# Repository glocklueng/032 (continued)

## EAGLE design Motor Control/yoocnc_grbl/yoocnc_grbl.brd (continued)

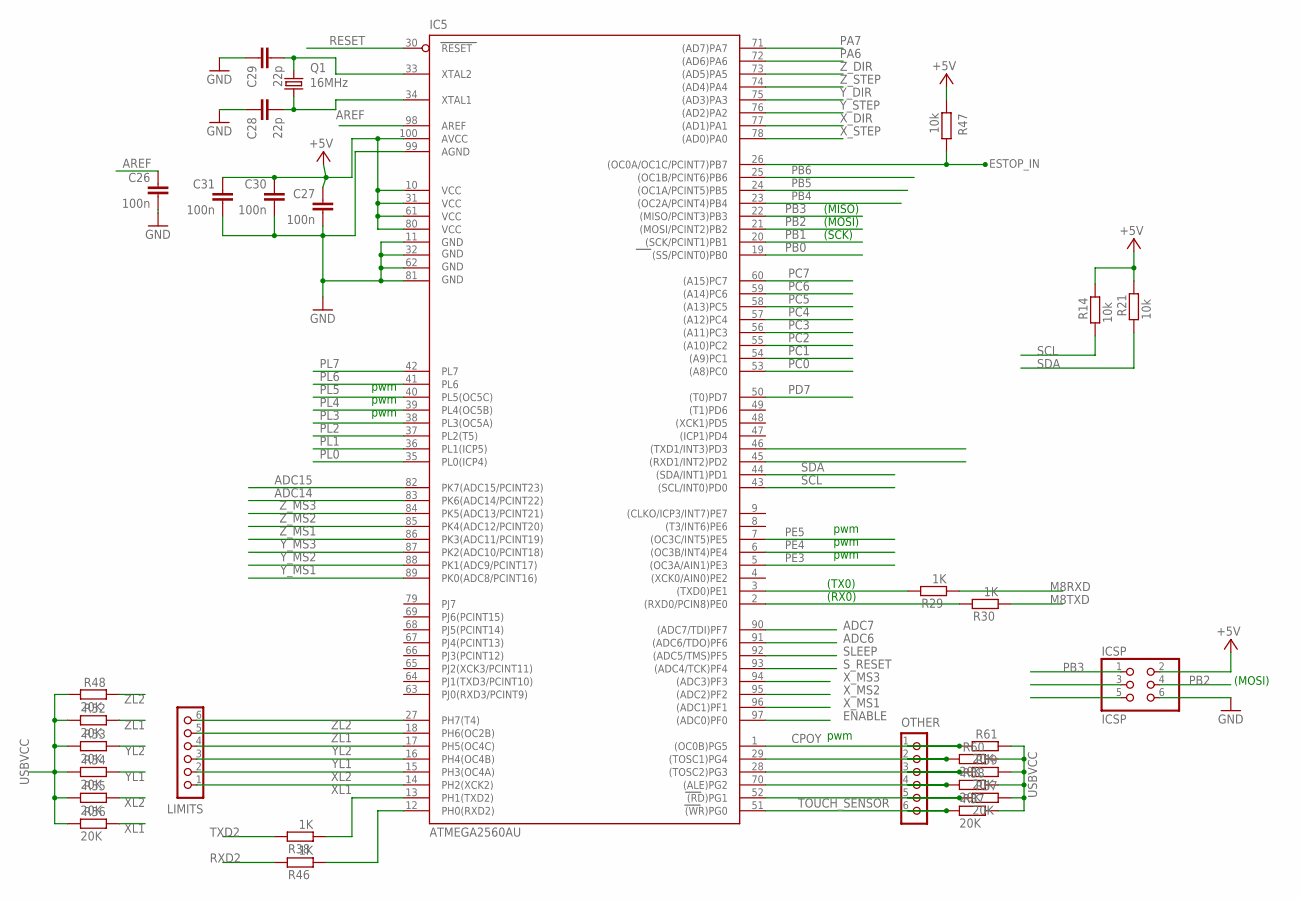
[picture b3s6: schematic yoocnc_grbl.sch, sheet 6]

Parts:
C26, C27, C30, C31: 100n; C0805K; PARTNO CC0805ZRY5V9BB104
C28, C29: 22p; C0805K; PARTNO C0805C220J5GACTU
IC5: ATMEGA2560AU; TQFP100; PARTNO ATMEGA256RZBV-8AU
ICSP: ICSP; 2X03; PARTNO *
LIMITS: CON_HEADER_1X06-PTH; M1X6; PARTNO *
OTHER: CON_HEADER_1X06-PTH; M1X6; PARTNO *
Q1: 16MHz; SM49; PARTNO ABLS-16.000MHZ-B4-T
R14, R21, R47: 10k; R0805W; PARTNO RC0805JR-0710KL
R29, R30, R38, R46: 1K; R0805W; PARTNO RC0805JR-0710KL
R37, R48, R52, R53, R54, R55, R56, R57, R58, R59, R60, R61: 20K; R0603; PARTNO RC0805JR-0710KL

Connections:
ADC6: IC5.91 ((ADC6/TDO)PF6)
ADC7: IC5.90 ((ADC7/TDI)PF7)
ADC14: IC5.83 (PK6(ADC14/PCINT22))
ADC15: IC5.82 (PK7(ADC15/PCINT23))
AREF: C26.1, IC5.98 (AREF)
CPOY: IC5.1 ((OC0B)PG5), OTHER.1, R61.2
ENABLE: IC5.97 ((ADC0)PF0); also elsewhere on the board
ESTOP_IN: IC5.26 ((OC0A/OC1C/PCINT7)PB7), R47.1; also elsewhere on the board
GND: C26.2, C27.2, C28.1, C29.1, C30.2, C31.2, IC5.11 (GND), IC5.32 (GND1), IC5.62 (GND2), IC5.81 (GND3), IC5.99 (AGND), ICSP.6; also elsewhere on the board
M8RXD: R29.2; also elsewhere on the board
M8TXD: R30.2; also elsewhere on the board
unnamed: IC5.29 ((TOSC1)PG4), OTHER.2, R60.2
unnamed: IC5.28 ((TOSC2)PG3), OTHER.3, R59.2
unnamed: IC5.3 ((TXD0)PE1), R29.1
unnamed: IC5.2 ((RXD0/PCIN8)PE0), R30.1
unnamed: IC5.70 ((ALE)PG2), OTHER.4, R58.2
unnamed: IC5.52 ((RD)PG1), OTHER.5, R57.2
unnamed: IC5.13 (PH1(TXD2)), R38.2
unnamed: IC5.12 (PH0(RXD2)), R46.2
unnamed: C28.2, IC5.34 (XTAL1)
unnamed: C29.2, IC5.33 (XTAL2)
PA6: IC5.72 ((AD6)PA6)
PA7: IC5.71 ((AD7)PA7)
PB0: IC5.19 ((SS/PCINT0)PB0)
PB1: IC5.20 ((SCK/PCINT1)PB1), ICSP.3
PB2: IC5.21 ((MOSI/PCINT2)PB2), ICSP.4
PB3: IC5.22 ((MISO/PCINT3)PB3), ICSP.1
PB4: IC5.23 ((OC2A/PCINT4)PB4)
PB5: IC5.24 ((OC1A/PCINT5)PB5)
PB6: IC5.25 ((OC1B/PCINT6)PB6)
PC0: IC5.53 ((A8)PC0)
PC1: IC5.54 ((A9)PC1)
PC2: IC5.55 ((A10)PC2)
PC3: IC5.56 ((A11)PC3)
PC4: IC5.57 ((A12)PC4)
PC5: IC5.58 ((A13)PC5)
PC6: IC5.59 ((A14)PC6)
PC7: IC5.60 ((A15)PC7)
PD7: IC5.50 ((T0)PD7)
PE3: IC5.5 ((OC3A/AIN1)PE3)
PE4: IC5.6 ((OC3B/INT4)PE4)
PE5: IC5.7 ((OC3C/INT5)PE5)
PL0: IC5.35 (PL0(ICP4))
PL1: IC5.36 (PL1(ICP5))
PL2: IC5.37 (PL2(T5))
PL3: IC5.38 (PL3(OC5A))
PL4: IC5.39 (PL4(OC5B))
PL5: IC5.40 (PL5(OC5C))
PL6: IC5.41 (PL6)
PL7: IC5.42 (PL7)
RESET: IC5.30 (RESET), ICSP.5; also elsewhere on the board
RXD1: IC5.45 ((RXD1/INT2)PD2)
RXD2: R46.1; also elsewhere on the board
SCL: IC5.43 ((SCL/INT0)PD0), R14.2
SDA: IC5.44 ((SDA/INT1)PD1), R21.2
SLEEP: IC5.92 ((ADC5/TMS)PF5); also elsewhere on the board
S_RESET: IC5.93 ((ADC4/TCK)PF4); also elsewhere on the board
TOUCH_SENSOR: IC5.51 ((WR)PG0), OTHER.6, R37.2
TXD1: IC5.46 ((TXD1/INT3)PD3)
TXD2: R38.1; also elsewhere on the board
USBVCC: C27.1, C30.1, C31.1, IC5.10 (VCC), IC5.31 (VCC1), IC5.61 (VCC2), IC5.80 (VCC3), IC5.100 (AVCC), ICSP.2, R14.1, R21.1, R37.1, R47.2, R48.2, R52.2, R53.2, R54.2, R55.2, R56.2, R57.1, R58.1, R59.1, R60.1, R61.1; also elsewhere on the board
XL1: IC5.14 (PH2(XCK2)), LIMITS.1, R56.1
XL2: IC5.15 (PH3(OC4A)), LIMITS.2, R55.1
X_DIR: IC5.77 ((AD1)PA1); also elsewhere on the board
X_MS1: IC5.96 ((ADC1)PF1); also elsewhere on the board
X_MS2: IC5.95 ((ADC2)PF2); also elsewhere on the board
X_MS3: IC5.94 ((ADC3)PF3); also elsewhere on the board
X_STEP: IC5.78 ((AD0)PA0); also elsewhere on the board
YL1: IC5.16 (PH4(OC4B)), LIMITS.3, R54.1
YL2: IC5.17 (PH5(OC4C)), LIMITS.4, R53.1
Y_DIR: IC5.75 ((AD3)PA3); also elsewhere on the board
Y_MS1: IC5.89 (PK0(ADC8/PCINT16)); also elsewhere on the board
Y_MS2: IC5.88 (PK1(ADC9/PCINT17)); also elsewhere on the board
Y_MS3: IC5.87 (PK2(ADC10/PCINT18)); also elsewhere on the board
Y_STEP: IC5.76 ((AD2)PA2); also elsewhere on the board
ZL1: IC5.18 (PH6(OC2B)), LIMITS.5, R52.1
ZL2: IC5.27 (PH7(T4)), LIMITS.6, R48.1
Z_DIR: IC5.73 ((AD5)PA5); also elsewhere on the board
Z_MS1: IC5.86 (PK3(ADC11/PCINT19)); also elsewhere on the board
Z_MS2: IC5.85 (PK4(ADC12/PCINT20)); also elsewhere on the board
Z_MS3: IC5.84 (PK5(ADC13/PCINT21)); also elsewhere on the board
Z_STEP: IC5.74 ((AD4)PA4); also elsewhere on the board

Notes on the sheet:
pwm
(TX0)
(RX0)
(MISO)
(SCK)
(MOSI)

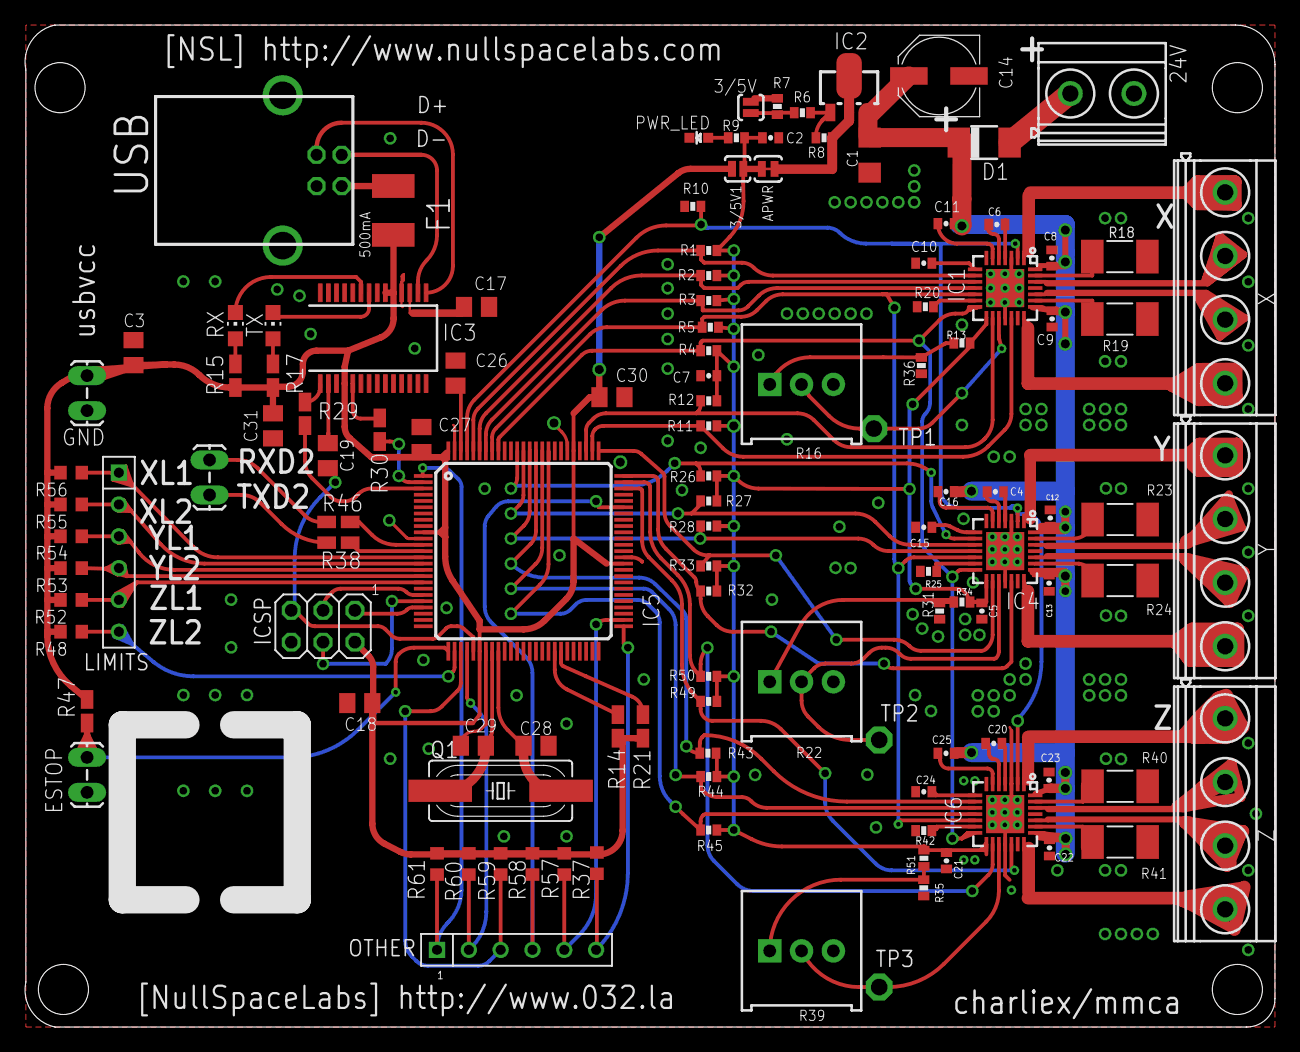
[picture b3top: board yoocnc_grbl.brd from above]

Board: 2 copper layers, 99.8 x 80.0 mm, 121 parts (0 on the bottom side), 105 nets.

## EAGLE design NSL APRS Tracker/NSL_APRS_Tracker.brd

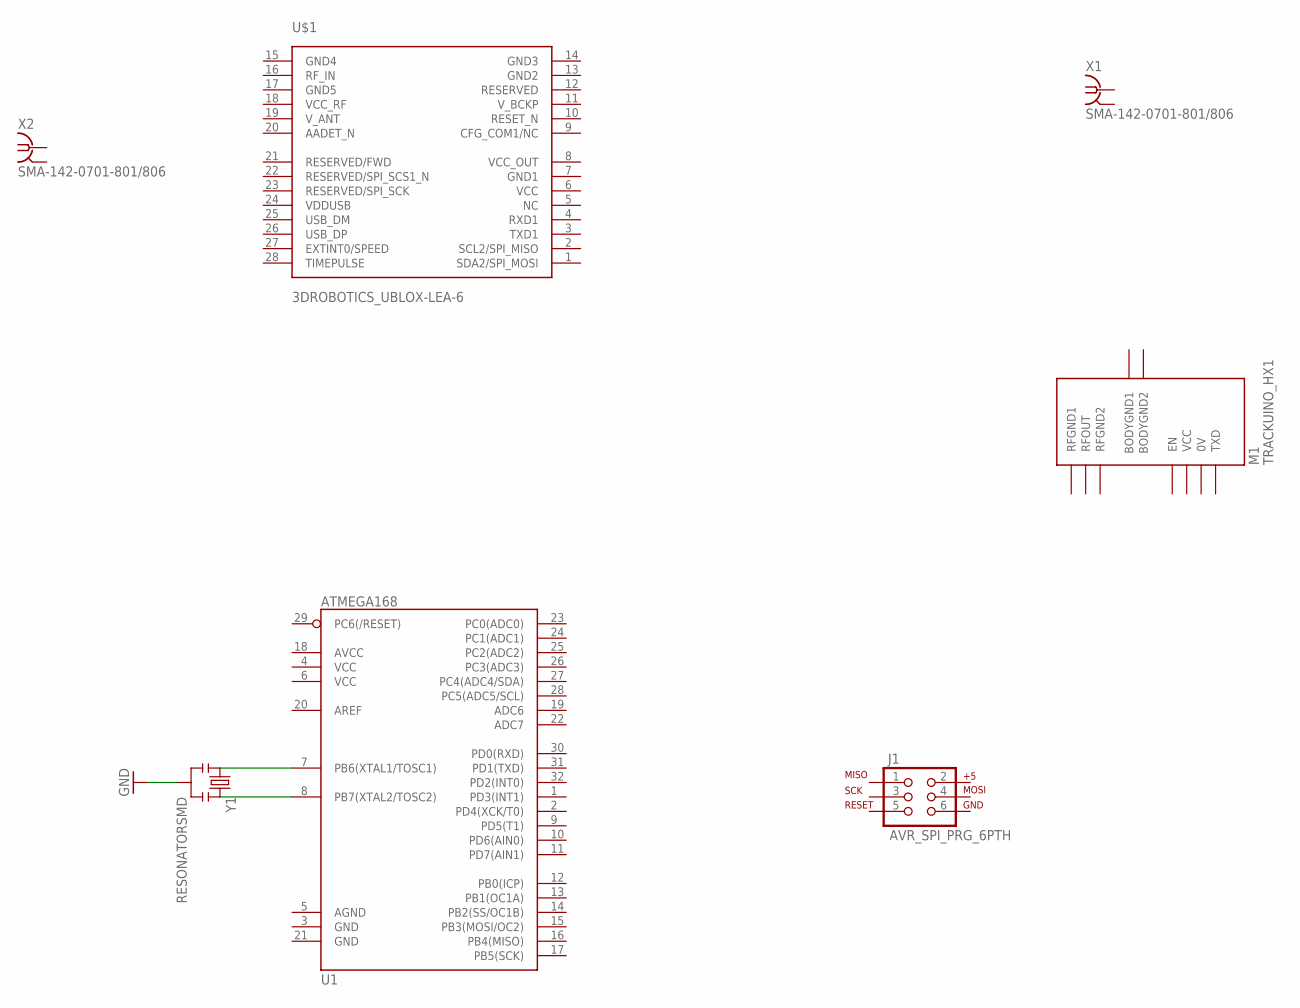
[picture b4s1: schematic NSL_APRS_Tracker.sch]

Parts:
J1: AVR_SPI_PRG_6PTH; 2X3
M1: TRACKUINO_HX1
U1: ATMEGA168; TQFP32-08
U$1: 3DROBOTICS_UBLOX-LEA-6
X1, X2: SMA-142-0701-801/806; J502-ND-142-0701-801/806
Y1: RESONATORSMD; RESONATOR-SMD

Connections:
GND: X1.G@1 (GND), X1.G@2 (GND), X1.G@3 (GND), X1.G@4 (GND), X2.G@1 (GND), X2.G@2 (GND), X2.G@3 (GND), X2.G@4 (GND), Y1.2
unnamed: U1.7 (PB6(XTAL1/TOSC1)), Y1.1
unnamed: U1.8 (PB7(XTAL2/TOSC2)), Y1.3

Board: 2 copper layers, 7 parts (0 on the bottom side), 3 nets, no tracks yet.
